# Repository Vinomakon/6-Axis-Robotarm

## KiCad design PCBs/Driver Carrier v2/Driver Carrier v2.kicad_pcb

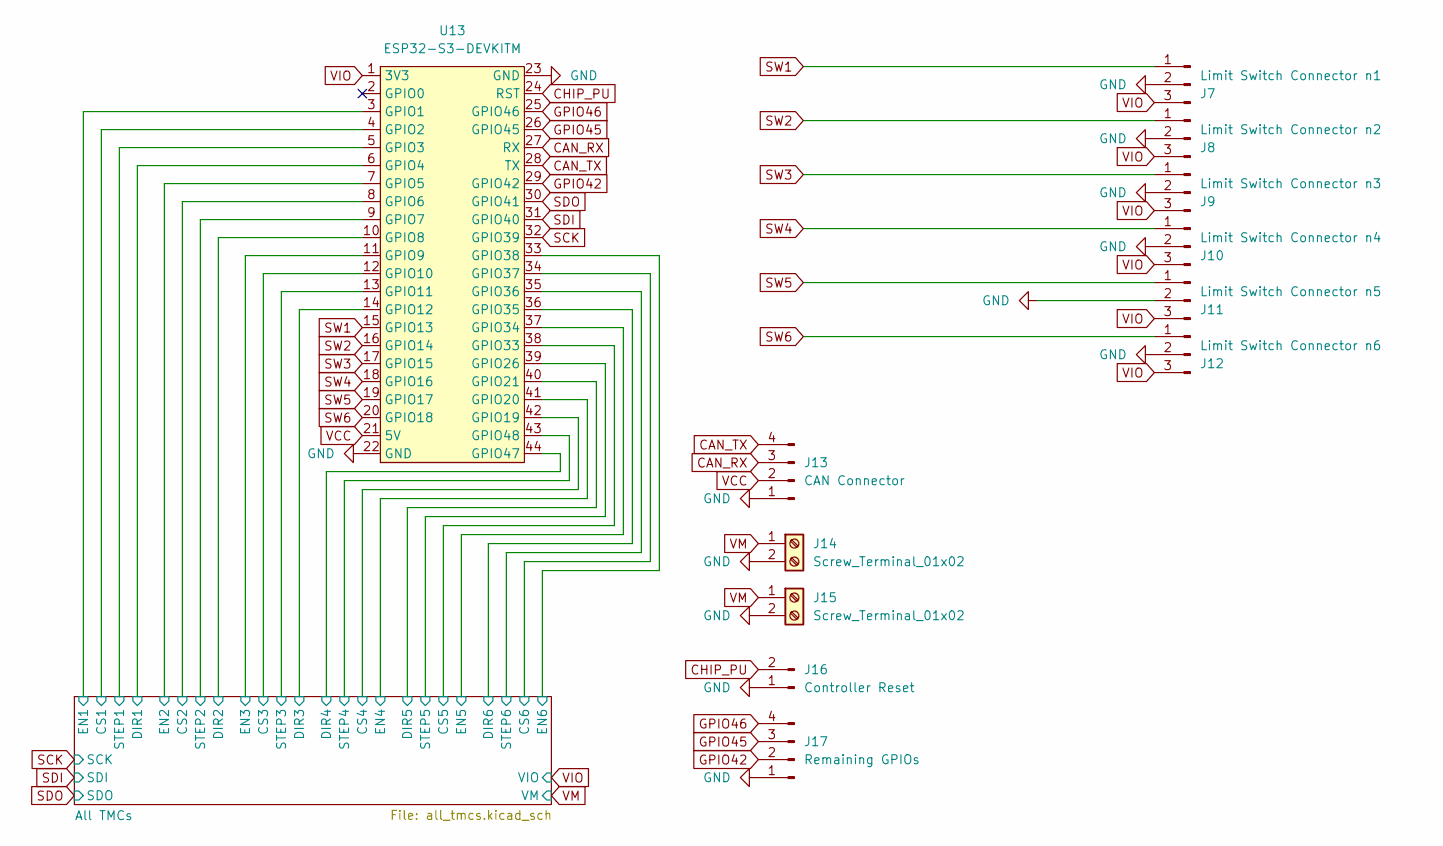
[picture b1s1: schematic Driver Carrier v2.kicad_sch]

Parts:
J7: Limit Switch Connector n1; PinHeader_1x03_P2.54mm_Vertical
J8: Limit Switch Connector n2; PinHeader_1x03_P2.54mm_Vertical
J9: Limit Switch Connector n3; PinHeader_1x03_P2.54mm_Vertical
J10: Limit Switch Connector n4; PinHeader_1x03_P2.54mm_Vertical
J11: Limit Switch Connector n5; PinHeader_1x03_P2.54mm_Vertical
J12: Limit Switch Connector n6; PinHeader_1x03_P2.54mm_Vertical
J13: CAN Connector; PinHeader_1x04_P2.54mm_Vertical
J14, J15: Screw_Terminal_01x02; Phoenix_TerminalBlock_1x02_3.5mm_1984617
J16: Controller Reset; PinHeader_1x02_P2.54mm_Vertical
J17: Remaining GPIOs; PinHeader_1x04_P2.54mm_Vertical
U13: ESP32-S3-DEVKITM; ESP32-S3-DEVKITM Female Headers

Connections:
/All TMCs/CS1: U13.4 (GPIO2); also elsewhere on the board
/All TMCs/CS2: U13.8 (GPIO6); also elsewhere on the board
/All TMCs/CS3: U13.12 (GPIO10); also elsewhere on the board
/All TMCs/CS4: U13.42 (GPIO19); also elsewhere on the board
/All TMCs/CS5: U13.38 (GPIO33); also elsewhere on the board
/All TMCs/CS6: U13.34 (GPIO37); also elsewhere on the board
/All TMCs/DIR1: U13.6 (GPIO4); also elsewhere on the board
/All TMCs/DIR2: U13.10 (GPIO8); also elsewhere on the board
/All TMCs/DIR3: U13.14 (GPIO12); also elsewhere on the board
/All TMCs/DIR4: U13.44 (GPIO47); also elsewhere on the board
/All TMCs/DIR5: U13.40 (GPIO21); also elsewhere on the board
/All TMCs/DIR6: U13.36 (GPIO35); also elsewhere on the board
/All TMCs/EN1: U13.3 (GPIO1); also elsewhere on the board
/All TMCs/EN2: U13.7 (GPIO5); also elsewhere on the board
/All TMCs/EN3: U13.11 (GPIO9); also elsewhere on the board
/All TMCs/EN4: U13.41 (GPIO20); also elsewhere on the board
/All TMCs/EN5: U13.37 (GPIO34); also elsewhere on the board
/All TMCs/EN6: U13.33 (GPIO38); also elsewhere on the board
/All TMCs/STEP1: U13.5 (GPIO3); also elsewhere on the board
/All TMCs/STEP2: U13.9 (GPIO7); also elsewhere on the board
/All TMCs/STEP3: U13.13 (GPIO11); also elsewhere on the board
/All TMCs/STEP4: U13.43 (GPIO48); also elsewhere on the board
/All TMCs/STEP5: U13.39 (GPIO26); also elsewhere on the board
/All TMCs/STEP6: U13.35 (GPIO36); also elsewhere on the board
CAN_RX: J13.3, U13.27 (RX)
CAN_TX: J13.4, U13.28 (TX)
CHIP_PU: J16.2, U13.24 (RST)
GND: J7.2, J8.2, J9.2, J10.2, J11.2, J12.2, J13.1, J14.2, J15.2, J16.1, J17.1, U13.22 (GND), U13.23 (GND); also elsewhere on the board
GPIO42: J17.2, U13.29 (GPIO42)
GPIO45: J17.3, U13.26 (GPIO45)
GPIO46: J17.4, U13.25 (GPIO46)
SCK: U13.32 (GPIO39); also elsewhere on the board
SDI: U13.31 (GPIO40); also elsewhere on the board
SDO: U13.30 (GPIO41); also elsewhere on the board
SW1: J7.1, U13.15 (GPIO13)
SW2: J8.1, U13.16 (GPIO14)
SW3: J9.1, U13.17 (GPIO15)
SW4: J10.1, U13.18 (GPIO16)
SW5: J11.1, U13.19 (GPIO17)
SW6: J12.1, U13.20 (GPIO18)
VCC: J13.2, U13.21 (5V)
VIO: J7.3, J8.3, J9.3, J10.3, J11.3, J12.3, U13.1 (3V3); also elsewhere on the board
VM: J14.1, J15.1; also elsewhere on the board

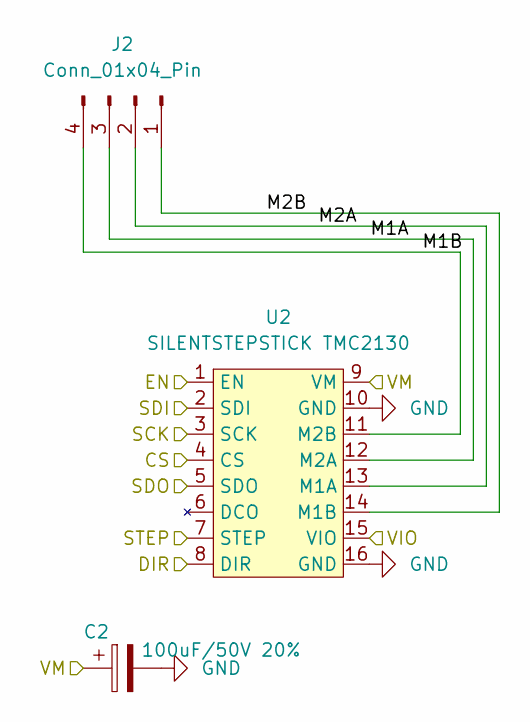
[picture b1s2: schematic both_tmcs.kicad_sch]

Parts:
C2: 100uF/50V 20%; CP_Radial_D8.0mm_P3.50mm
J2: Conn_01x04_Pin; PinHeader_1x04_P2.54mm_Vertical
U2: SILENTSTEPSTICK TMC2130; Digikey PartN TMCSILENTSTEPSTICK SPI

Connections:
/All TMCs/BothTMCs n2/M1A: J2.3, U2.12 (M2A)
/All TMCs/BothTMCs n2/M1B: J2.4, U2.11 (M2B)
/All TMCs/BothTMCs n2/M2A: J2.2, U2.13 (M1A)
/All TMCs/BothTMCs n2/M2B: J2.1, U2.14 (M1B)
/All TMCs/CS2: U2.4 (CS); also elsewhere on the board
/All TMCs/DIR2: U2.8 (DIR); also elsewhere on the board
/All TMCs/EN2: U2.1 (EN); also elsewhere on the board
/All TMCs/STEP2: U2.7 (STEP); also elsewhere on the board
GND: C2.2, U2.10 (GND), U2.16 (GND); also elsewhere on the board
SCK: U2.3 (SCK); also elsewhere on the board
SDI: U2.2 (SDI); also elsewhere on the board
SDO: U2.5 (SDO); also elsewhere on the board
VIO: U2.15 (VIO); also elsewhere on the board
VM: C2.1, U2.9 (VM); also elsewhere on the board

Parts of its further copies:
C1, C3, C4, C5, C6: 100uF/50V 20%; CP_Radial_D8.0mm_P3.50mm
J1, J3, J4, J5, J6: Conn_01x04_Pin; PinHeader_1x04_P2.54mm_Vertical
U1, U3, U4, U5, U6: SILENTSTEPSTICK TMC2130; Digikey PartN TMCSILENTSTEPSTICK SPI

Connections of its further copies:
/All TMCs/BothTMCs n1/M1A: J1.3, U1.12 (M2A)
/All TMCs/BothTMCs n1/M1B: J1.4, U1.11 (M2B)
/All TMCs/BothTMCs n1/M2A: J1.2, U1.13 (M1A)
/All TMCs/BothTMCs n1/M2B: J1.1, U1.14 (M1B)
/All TMCs/BothTMCs n3/M1A: J3.3, U3.12 (M2A)
/All TMCs/BothTMCs n3/M1B: J3.4, U3.11 (M2B)
/All TMCs/BothTMCs n3/M2A: J3.2, U3.13 (M1A)
/All TMCs/BothTMCs n3/M2B: J3.1, U3.14 (M1B)
/All TMCs/BothTMCs n4/M1A: J4.3, U4.12 (M2A)
/All TMCs/BothTMCs n4/M1B: J4.4, U4.11 (M2B)
/All TMCs/BothTMCs n4/M2A: J4.2, U4.13 (M1A)
/All TMCs/BothTMCs n4/M2B: J4.1, U4.14 (M1B)
/All TMCs/BothTMCs n5/M1A: J5.3, U5.12 (M2A)
/All TMCs/BothTMCs n5/M1B: J5.4, U5.11 (M2B)
/All TMCs/BothTMCs n5/M2A: J5.2, U5.13 (M1A)
/All TMCs/BothTMCs n5/M2B: J5.1, U5.14 (M1B)
/All TMCs/BothTMCs n6/M1A: J6.3, U6.12 (M2A)
/All TMCs/BothTMCs n6/M1B: J6.4, U6.11 (M2B)
/All TMCs/BothTMCs n6/M2A: J6.2, U6.13 (M1A)
/All TMCs/BothTMCs n6/M2B: J6.1, U6.14 (M1B)
/All TMCs/CS1: U1.4 (CS); also elsewhere on the board
/All TMCs/CS3: U3.4 (CS); also elsewhere on the board
/All TMCs/CS4: U4.4 (CS); also elsewhere on the board
/All TMCs/CS5: U5.4 (CS); also elsewhere on the board
/All TMCs/CS6: U6.4 (CS); also elsewhere on the board
/All TMCs/DIR1: U1.8 (DIR); also elsewhere on the board
/All TMCs/DIR3: U3.8 (DIR); also elsewhere on the board
/All TMCs/DIR4: U4.8 (DIR); also elsewhere on the board
/All TMCs/DIR5: U5.8 (DIR); also elsewhere on the board
/All TMCs/DIR6: U6.8 (DIR); also elsewhere on the board
/All TMCs/EN1: U1.1 (EN); also elsewhere on the board
/All TMCs/EN3: U3.1 (EN); also elsewhere on the board
/All TMCs/EN4: U4.1 (EN); also elsewhere on the board
/All TMCs/EN5: U5.1 (EN); also elsewhere on the board
/All TMCs/EN6: U6.1 (EN); also elsewhere on the board
/All TMCs/STEP1: U1.7 (STEP); also elsewhere on the board
/All TMCs/STEP3: U3.7 (STEP); also elsewhere on the board
/All TMCs/STEP4: U4.7 (STEP); also elsewhere on the board
/All TMCs/STEP5: U5.7 (STEP); also elsewhere on the board
/All TMCs/STEP6: U6.7 (STEP); also elsewhere on the board
GND: C1.2, C3.2, C4.2, C5.2, C6.2, U1.10 (GND), U1.16 (GND), U3.10 (GND), U3.16 (GND), U4.10 (GND), U4.16 (GND), U5.10 (GND), U5.16 (GND), U6.10 (GND), U6.16 (GND); also elsewhere on the board
SCK: U1.3 (SCK), U3.3 (SCK), U4.3 (SCK), U5.3 (SCK), U6.3 (SCK); also elsewhere on the board
SDI: U1.2 (SDI), U3.2 (SDI), U4.2 (SDI), U5.2 (SDI), U6.2 (SDI); also elsewhere on the board
SDO: U1.5 (SDO), U3.5 (SDO), U4.5 (SDO), U5.5 (SDO), U6.5 (SDO); also elsewhere on the board
VIO: U1.15 (VIO), U3.15 (VIO), U4.15 (VIO), U5.15 (VIO), U6.15 (VIO); also elsewhere on the board
VM: C1.1, C3.1, C4.1, C5.1, C6.1, U1.9 (VM), U3.9 (VM), U4.9 (VM), U5.9 (VM), U6.9 (VM); also elsewhere on the board

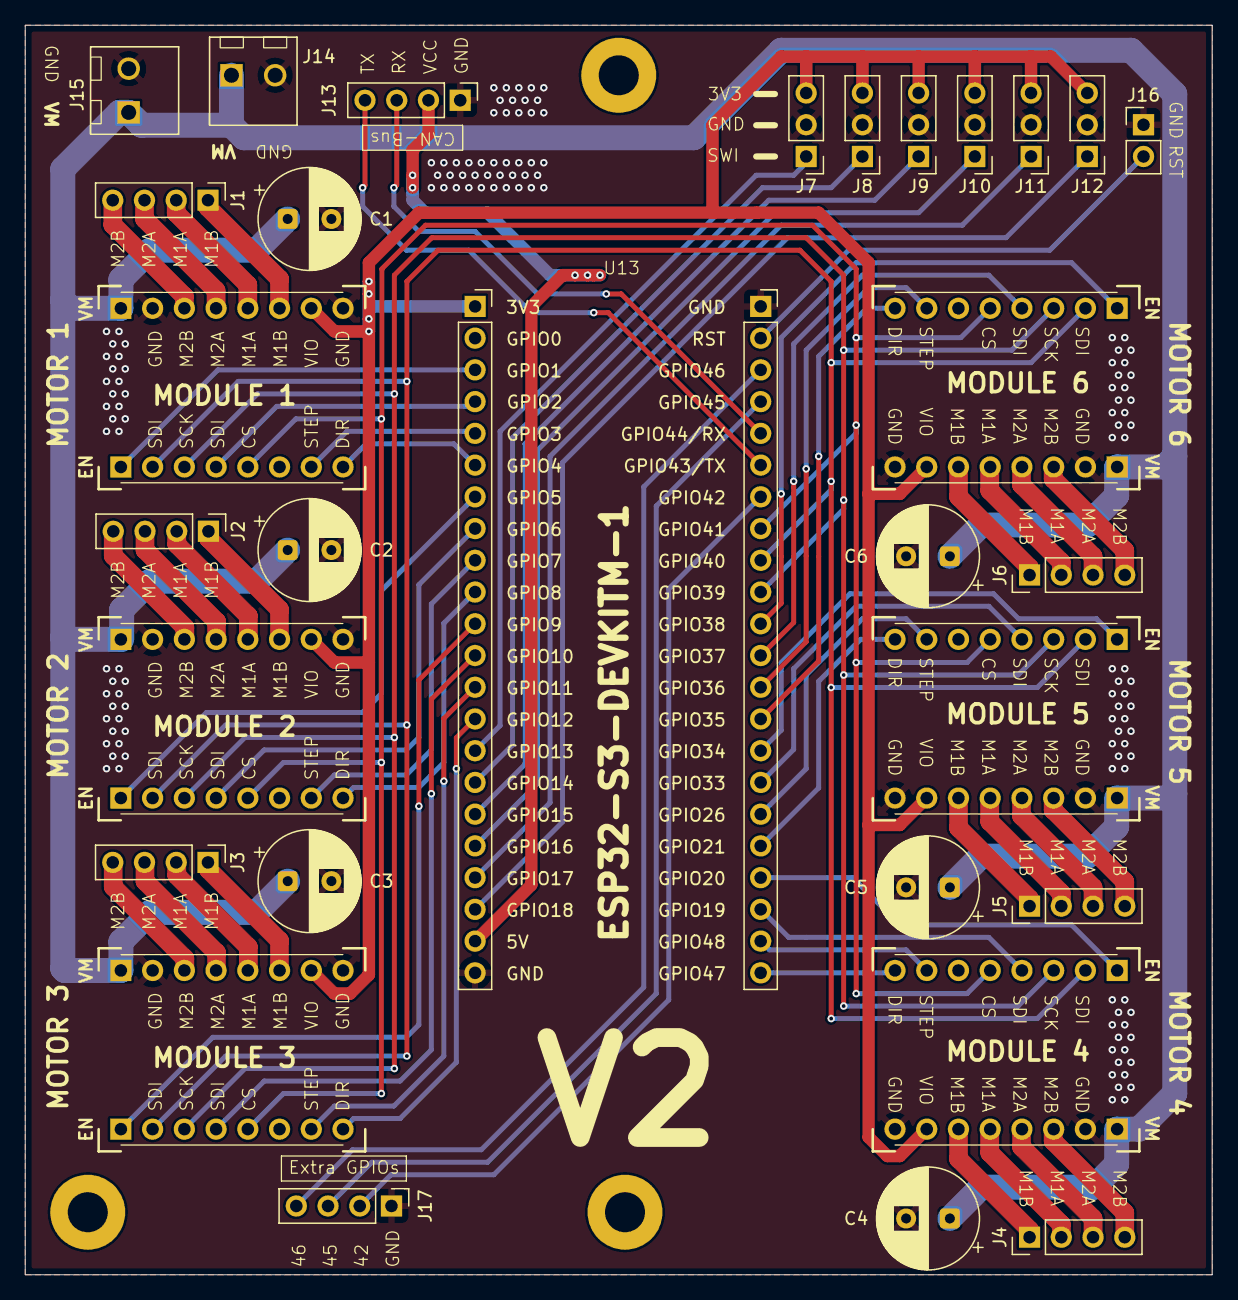
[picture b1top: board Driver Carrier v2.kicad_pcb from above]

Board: 2 copper layers, 95.0 x 100.0 mm, 30 parts (0 on the bottom side), 67 nets.

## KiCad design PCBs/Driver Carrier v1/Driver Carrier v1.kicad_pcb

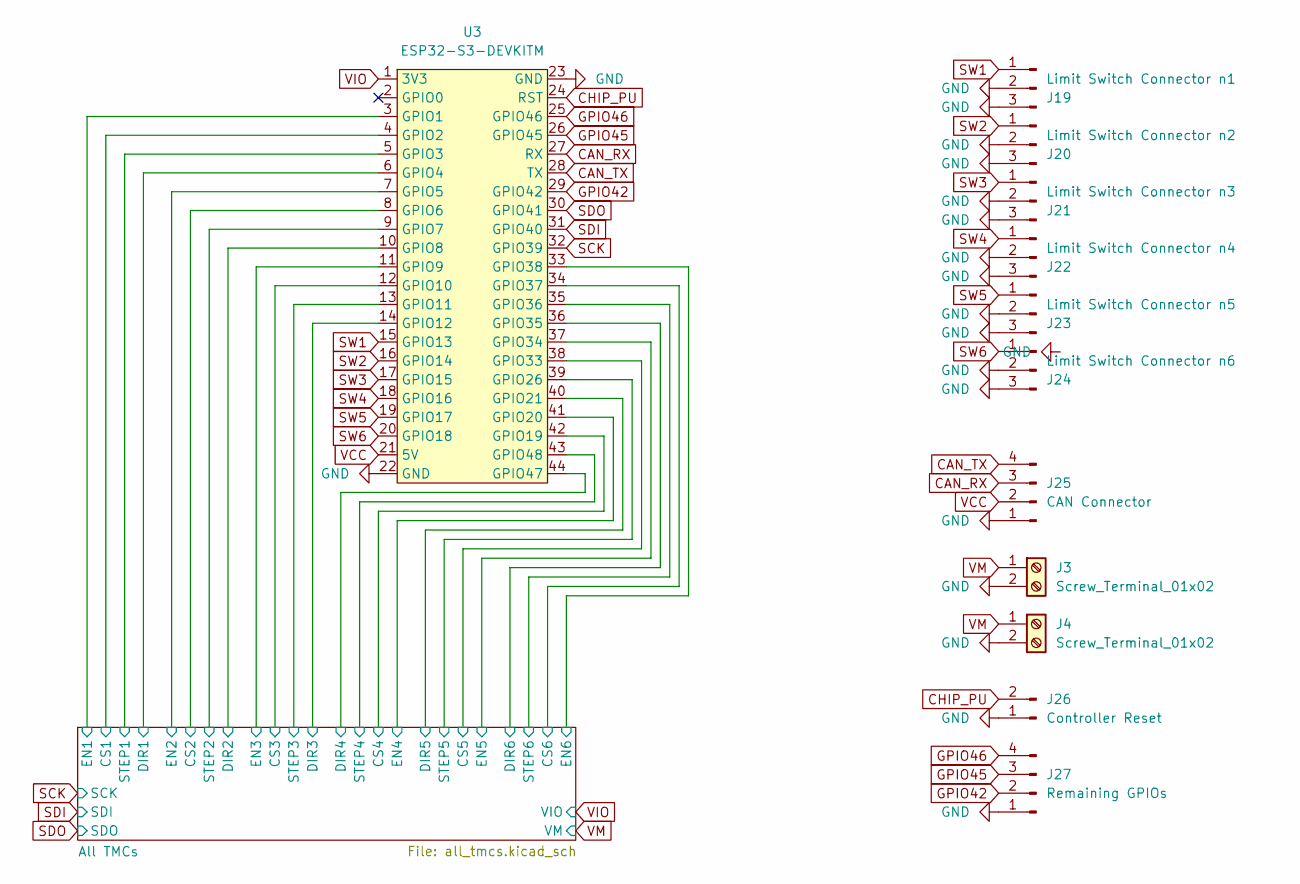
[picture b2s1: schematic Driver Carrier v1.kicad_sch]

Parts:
J3, J4: Screw_Terminal_01x02; Phoenix_TerminalBlock_1x02_3.5mm_1984617
J19: Limit Switch Connector n1; PinHeader_1x03_P2.54mm_Vertical
J20: Limit Switch Connector n2; PinHeader_1x03_P2.54mm_Vertical
J21: Limit Switch Connector n3; PinHeader_1x03_P2.54mm_Vertical
J22: Limit Switch Connector n4; PinHeader_1x03_P2.54mm_Vertical
J23: Limit Switch Connector n5; PinHeader_1x03_P2.54mm_Vertical
J24: Limit Switch Connector n6; PinHeader_1x03_P2.54mm_Vertical
J25: CAN Connector; PinHeader_1x04_P2.54mm_Vertical
J26: Controller Reset; PinHeader_1x02_P2.54mm_Vertical
J27: Remaining GPIOs; PinHeader_1x04_P2.54mm_Vertical
U3: ESP32-S3-DEVKITM; ESP32-S3-DEVKITM Female Headers

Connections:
/All TMCs/CS1: U3.4 (GPIO2); also elsewhere on the board
/All TMCs/CS2: U3.8 (GPIO6); also elsewhere on the board
/All TMCs/CS3: U3.12 (GPIO10); also elsewhere on the board
/All TMCs/CS4: U3.42 (GPIO19); also elsewhere on the board
/All TMCs/CS5: U3.38 (GPIO33); also elsewhere on the board
/All TMCs/CS6: U3.34 (GPIO37); also elsewhere on the board
/All TMCs/DIR1: U3.6 (GPIO4); also elsewhere on the board
/All TMCs/DIR2: U3.10 (GPIO8); also elsewhere on the board
/All TMCs/DIR3: U3.14 (GPIO12); also elsewhere on the board
/All TMCs/DIR4: U3.44 (GPIO47); also elsewhere on the board
/All TMCs/DIR5: U3.40 (GPIO21); also elsewhere on the board
/All TMCs/DIR6: U3.36 (GPIO35); also elsewhere on the board
/All TMCs/EN1: U3.3 (GPIO1); also elsewhere on the board
/All TMCs/EN2: U3.7 (GPIO5); also elsewhere on the board
/All TMCs/EN3: U3.11 (GPIO9); also elsewhere on the board
/All TMCs/EN4: U3.41 (GPIO20); also elsewhere on the board
/All TMCs/EN5: U3.37 (GPIO34); also elsewhere on the board
/All TMCs/EN6: U3.33 (GPIO38); also elsewhere on the board
/All TMCs/STEP1: U3.5 (GPIO3); also elsewhere on the board
/All TMCs/STEP2: U3.9 (GPIO7); also elsewhere on the board
/All TMCs/STEP3: U3.13 (GPIO11); also elsewhere on the board
/All TMCs/STEP4: U3.43 (GPIO48); also elsewhere on the board
/All TMCs/STEP5: U3.39 (GPIO26); also elsewhere on the board
/All TMCs/STEP6: U3.35 (GPIO36); also elsewhere on the board
CAN_RX: J25.3, U3.27 (RX)
CAN_TX: J25.4, U3.28 (TX)
CHIP_PU: J26.2, U3.24 (RST)
GND: J3.2, J4.2, J19.2, J19.3, J20.2, J20.3, J21.2, J21.3, J22.2, J22.3, J23.2, J23.3, J24.2, J24.3, J25.1, J26.1, J27.1, U3.22 (GND), U3.23 (GND); also elsewhere on the board
GPIO42: J27.2, U3.29 (GPIO42)
GPIO45: J27.3, U3.26 (GPIO45)
GPIO46: J27.4, U3.25 (GPIO46)
SCK: U3.32 (GPIO39); also elsewhere on the board
SDI: U3.31 (GPIO40); also elsewhere on the board
SDO: U3.30 (GPIO41); also elsewhere on the board
SW1: J19.1, U3.15 (GPIO13)
SW2: J20.1, U3.16 (GPIO14)
SW3: J21.1, U3.17 (GPIO15)
SW4: J22.1, U3.18 (GPIO16)
SW5: J23.1, U3.19 (GPIO17)
SW6: J24.1, U3.20 (GPIO18)
VCC: J25.2, U3.21 (5V)
VIO: U3.1 (3V3); also elsewhere on the board
VM: J3.1, J4.1; also elsewhere on the board

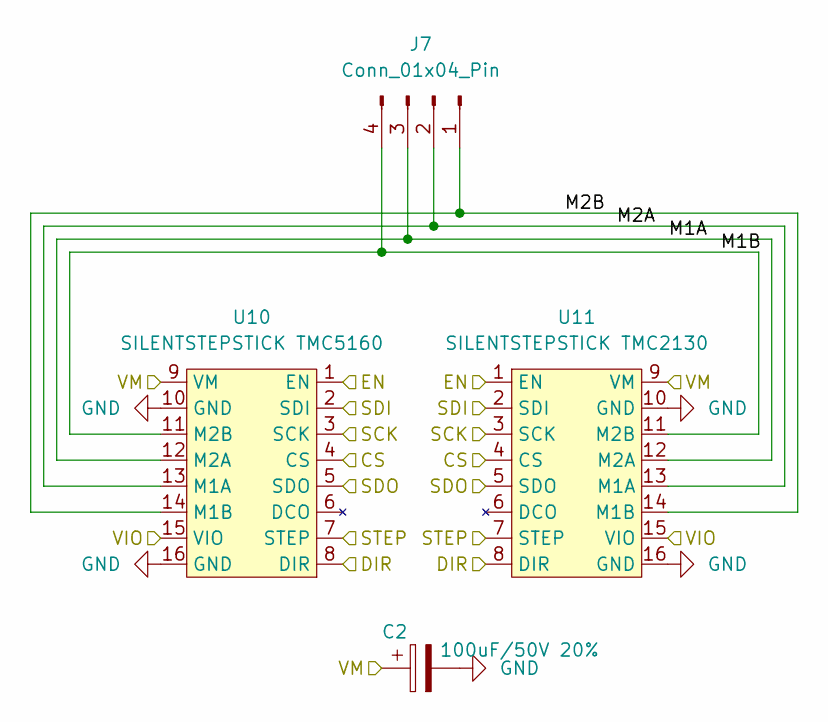
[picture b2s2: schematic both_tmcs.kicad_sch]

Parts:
C2: 100uF/50V 20%; CP_Radial_D8.0mm_P3.50mm
J7: Conn_01x04_Pin; PinHeader_1x04_P2.54mm_Vertical
U10: SILENTSTEPSTICK TMC5160; Digikey PartN TMC5160SILENTSTEPSTICK
U11: SILENTSTEPSTICK TMC2130; Digikey PartN TMCSILENTSTEPSTICK SPI

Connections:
/All TMCs/BothTMCs n2/M1A: J7.3, U10.12 (M2A), U11.12 (M2A)
/All TMCs/BothTMCs n2/M1B: J7.4, U10.11 (M2B), U11.11 (M2B)
/All TMCs/BothTMCs n2/M2A: J7.2, U10.13 (M1A), U11.13 (M1A)
/All TMCs/BothTMCs n2/M2B: J7.1, U10.14 (M1B), U11.14 (M1B)
/All TMCs/CS2: U10.4 (CS), U11.4 (CS); also elsewhere on the board
/All TMCs/DIR2: U10.8 (DIR), U11.8 (DIR); also elsewhere on the board
/All TMCs/EN2: U10.1 (EN), U11.1 (EN); also elsewhere on the board
/All TMCs/STEP2: U10.7 (STEP), U11.7 (STEP); also elsewhere on the board
GND: C2.2, U10.10 (GND), U10.16 (GND), U11.10 (GND), U11.16 (GND); also elsewhere on the board
SCK: U10.3 (SCK), U11.3 (SCK); also elsewhere on the board
SDI: U10.2 (SDI), U11.2 (SDI); also elsewhere on the board
SDO: U10.5 (SDO), U11.5 (SDO); also elsewhere on the board
VIO: U10.15 (VIO), U11.15 (VIO); also elsewhere on the board
VM: C2.1, U10.9 (VM), U11.9 (VM); also elsewhere on the board

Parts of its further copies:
C1, C3, C4, C5, C6: 100uF/50V 20%; CP_Radial_D8.0mm_P3.50mm
J6, J8, J9, J10, J11: Conn_01x04_Pin; PinHeader_1x04_P2.54mm_Vertical
U8, U12, U14, U16, U18: SILENTSTEPSTICK TMC5160; Digikey PartN TMC5160SILENTSTEPSTICK
U9, U13, U15, U17, U19: SILENTSTEPSTICK TMC2130; Digikey PartN TMCSILENTSTEPSTICK SPI

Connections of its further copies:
/All TMCs/BothTMCs n1/M1A: J6.3, U8.12 (M2A), U9.12 (M2A)
/All TMCs/BothTMCs n1/M1B: J6.4, U8.11 (M2B), U9.11 (M2B)
/All TMCs/BothTMCs n1/M2A: J6.2, U8.13 (M1A), U9.13 (M1A)
/All TMCs/BothTMCs n1/M2B: J6.1, U8.14 (M1B), U9.14 (M1B)
/All TMCs/BothTMCs n3/M1A: J10.3, U16.12 (M2A), U17.12 (M2A)
/All TMCs/BothTMCs n3/M1B: J10.4, U16.11 (M2B), U17.11 (M2B)
/All TMCs/BothTMCs n3/M2A: J10.2, U16.13 (M1A), U17.13 (M1A)
/All TMCs/BothTMCs n3/M2B: J10.1, U16.14 (M1B), U17.14 (M1B)
/All TMCs/BothTMCs n4/M1A: J8.3, U12.12 (M2A), U13.12 (M2A)
/All TMCs/BothTMCs n4/M1B: J8.4, U12.11 (M2B), U13.11 (M2B)
/All TMCs/BothTMCs n4/M2A: J8.2, U12.13 (M1A), U13.13 (M1A)
/All TMCs/BothTMCs n4/M2B: J8.1, U12.14 (M1B), U13.14 (M1B)
/All TMCs/BothTMCs n5/M1A: J9.3, U14.12 (M2A), U15.12 (M2A)
/All TMCs/BothTMCs n5/M1B: J9.4, U14.11 (M2B), U15.11 (M2B)
/All TMCs/BothTMCs n5/M2A: J9.2, U14.13 (M1A), U15.13 (M1A)
/All TMCs/BothTMCs n5/M2B: J9.1, U14.14 (M1B), U15.14 (M1B)
/All TMCs/BothTMCs n6/M1A: J11.3, U18.12 (M2A), U19.12 (M2A)
/All TMCs/BothTMCs n6/M1B: J11.4, U18.11 (M2B), U19.11 (M2B)
/All TMCs/BothTMCs n6/M2A: J11.2, U18.13 (M1A), U19.13 (M1A)
/All TMCs/BothTMCs n6/M2B: J11.1, U18.14 (M1B), U19.14 (M1B)
/All TMCs/CS1: U8.4 (CS), U9.4 (CS); also elsewhere on the board
/All TMCs/CS3: U16.4 (CS), U17.4 (CS); also elsewhere on the board
/All TMCs/CS4: U12.4 (CS), U13.4 (CS); also elsewhere on the board
/All TMCs/CS5: U14.4 (CS), U15.4 (CS); also elsewhere on the board
/All TMCs/CS6: U18.4 (CS), U19.4 (CS); also elsewhere on the board
/All TMCs/DIR1: U8.8 (DIR), U9.8 (DIR); also elsewhere on the board
/All TMCs/DIR3: U16.8 (DIR), U17.8 (DIR); also elsewhere on the board
/All TMCs/DIR4: U12.8 (DIR), U13.8 (DIR); also elsewhere on the board
/All TMCs/DIR5: U14.8 (DIR), U15.8 (DIR); also elsewhere on the board
/All TMCs/DIR6: U18.8 (DIR), U19.8 (DIR); also elsewhere on the board
/All TMCs/EN1: U8.1 (EN), U9.1 (EN); also elsewhere on the board
/All TMCs/EN3: U16.1 (EN), U17.1 (EN); also elsewhere on the board
/All TMCs/EN4: U12.1 (EN), U13.1 (EN); also elsewhere on the board
/All TMCs/EN5: U14.1 (EN), U15.1 (EN); also elsewhere on the board
/All TMCs/EN6: U18.1 (EN), U19.1 (EN); also elsewhere on the board
/All TMCs/STEP1: U8.7 (STEP), U9.7 (STEP); also elsewhere on the board
/All TMCs/STEP3: U16.7 (STEP), U17.7 (STEP); also elsewhere on the board
/All TMCs/STEP4: U12.7 (STEP), U13.7 (STEP); also elsewhere on the board
/All TMCs/STEP5: U14.7 (STEP), U15.7 (STEP); also elsewhere on the board
/All TMCs/STEP6: U18.7 (STEP), U19.7 (STEP); also elsewhere on the board
GND: C1.2, C3.2, C4.2, C5.2, C6.2, U8.10 (GND), U8.16 (GND), U9.10 (GND), U9.16 (GND), U12.10 (GND), U12.16 (GND), U13.10 (GND), U13.16 (GND), U14.10 (GND), U14.16 (GND), U15.10 (GND), U15.16 (GND), U16.10 (GND), U16.16 (GND), U17.10 (GND), U17.16 (GND), U18.10 (GND), U18.16 (GND), U19.10 (GND), U19.16 (GND); also elsewhere on the board
SCK: U8.3 (SCK), U9.3 (SCK), U12.3 (SCK), U13.3 (SCK), U14.3 (SCK), U15.3 (SCK), U16.3 (SCK), U17.3 (SCK), U18.3 (SCK), U19.3 (SCK); also elsewhere on the board
SDI: U8.2 (SDI), U9.2 (SDI), U12.2 (SDI), U13.2 (SDI), U14.2 (SDI), U15.2 (SDI), U16.2 (SDI), U17.2 (SDI), U18.2 (SDI), U19.2 (SDI); also elsewhere on the board
SDO: U8.5 (SDO), U9.5 (SDO), U12.5 (SDO), U13.5 (SDO), U14.5 (SDO), U15.5 (SDO), U16.5 (SDO), U17.5 (SDO), U18.5 (SDO), U19.5 (SDO); also elsewhere on the board
VIO: U8.15 (VIO), U9.15 (VIO), U12.15 (VIO), U13.15 (VIO), U14.15 (VIO), U15.15 (VIO), U16.15 (VIO), U17.15 (VIO), U18.15 (VIO), U19.15 (VIO); also elsewhere on the board
VM: C1.1, C3.1, C4.1, C5.1, C6.1, U8.9 (VM), U9.9 (VM), U12.9 (VM), U13.9 (VM), U14.9 (VM), U15.9 (VM), U16.9 (VM), U17.9 (VM), U18.9 (VM), U19.9 (VM); also elsewhere on the board

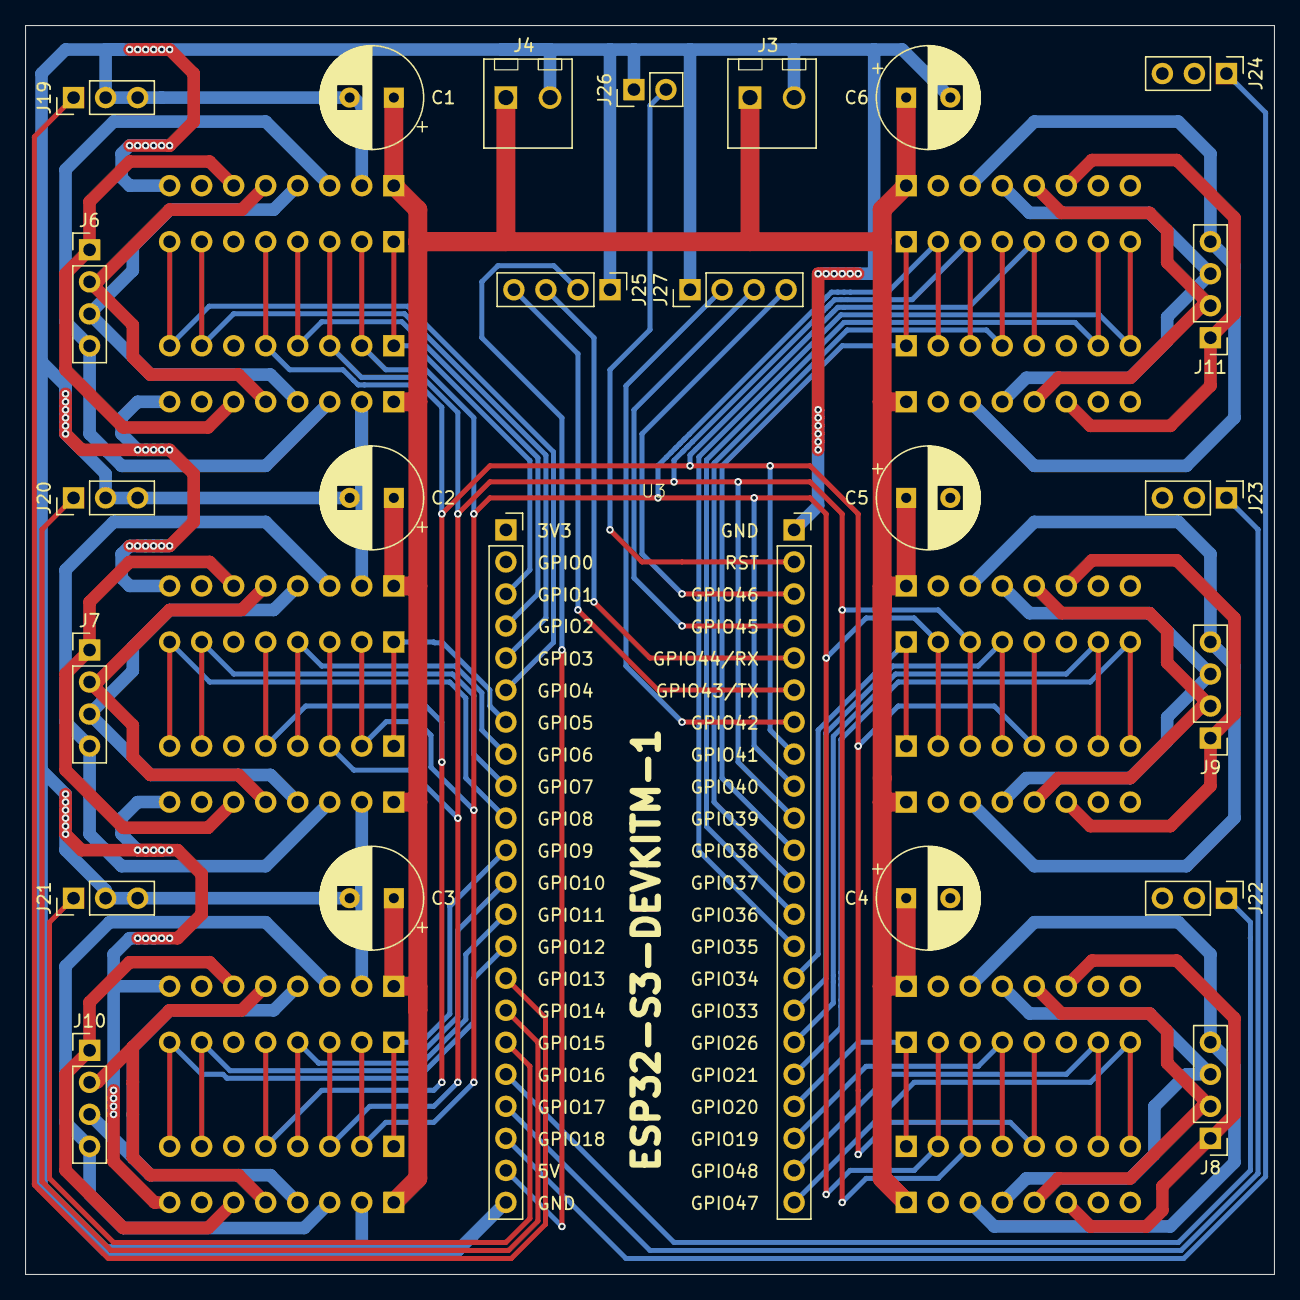
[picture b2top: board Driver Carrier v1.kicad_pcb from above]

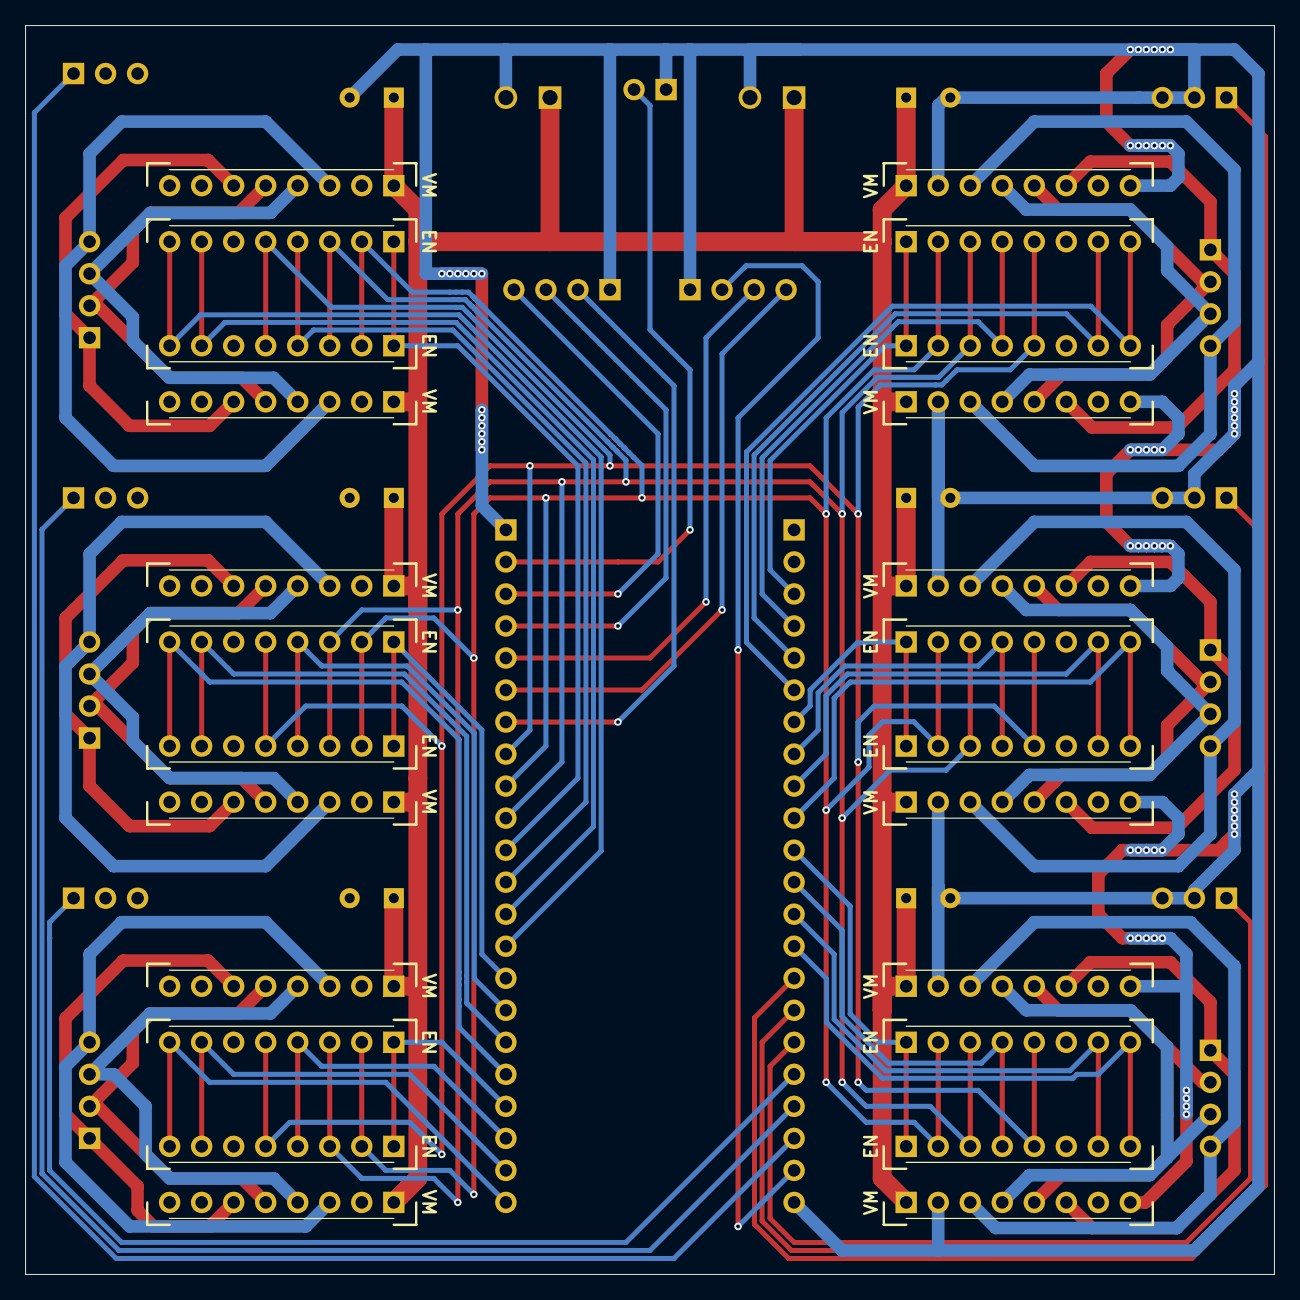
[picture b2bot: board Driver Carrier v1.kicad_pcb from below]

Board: 2 copper layers, 99.1 x 99.1 mm, 36 parts (12 on the bottom side), 67 nets.

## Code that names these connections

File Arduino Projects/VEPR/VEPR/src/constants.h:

// PINS FOR TMC-SPI
#define SDO_PIN 41
#define SCK_PIN 39
#define SDI_PIN 40

// PINS FOR MOTOR 1
#define DIR0_PIN 4
#define STEP0_PIN 3
#define EN0_PIN 1
#define CS0_PIN 2
#define SW0_PIN 13

// PINS FOR MOTOR 2
#define DIR1_PIN 8
#define STEP1_PIN 7
#define EN1_PIN 5
#define CS1_PIN 6
#define SW1_PIN 14

//PINS FOR MOTOR 3
#define DIR2_PIN 12
#define STEP2_PIN 11
#define EN2_PIN 9
#define CS2_PIN 10
#define SW2_PIN 15

//PINS FOR MOTOR 4
#define DIR3_PIN 47
#define STEP3_PIN 48
#define EN3_PIN 20
#define CS3_PIN 19
#define SW3_PIN 16

//PINS FOR MOTOR 5
#define DIR4_PIN 21
#define STEP4_PIN 26
#define EN4_PIN 34
#define CS4_PIN 33
#define SW4_PIN 17

//PINS FOR MOTOR 6
#define DIR5_PIN 35
#define STEP5_PIN 36
#define EN5_PIN 38
#define CS5_PIN 37
#define SW5_PIN 18

// VALUES FOR TMC
#define STALL_VALUE 15
#define R_SENSE 0.11f

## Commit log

2025-02-11 Commit Date: 11/2/2025
    Some small changes to the websockets code
2025-02-12 Added Homing Functionality
2025-02-12 Organization of Files
2025-02-13 Rewrote Main Code
    Instead of using my own code, I used the libraries "AccelStepper", "TMCStepper" and the built-in SPI function.
2025-02-14 Small Adjustments
2025-02-20 Added Big Motors
2025-02-20 Some little Improvements
2025-02-21 Integration of 3 more motors
    Still need to implement the synchrounous movement
2025-02-24 Started work on the next Carrier Board
2025-02-25 Continued working on the PCB
2025-02-26 Finished Driver Carrier
2025-02-26 Update Arbeitsjournal
2025-02-27 Unknown Changes
2025-04-14 Commit 14.04.2025
2025-04-16 New PCB and testing belt drive
2025-07-15 Progress 15.07
    A LOOOT of new things
2025-07-22 6th Motor Addition
    Python and Arduino
2025-07-22 6th Arm finished
2025-07-23 UI Redesign v1
2025-07-24 Heavy changes to the python script and C++ code
2025-07-24 hotfix individualmovement
2025-07-25 A looooooooooooot of Paramteres
2025-07-25 Kindofworking
2025-07-25 Current Limiting fix
2025-07-25 Splitting the parameter submission
2025-07-31 Preparing for 3rd prototype
    Preparing for 3rd prototype and starting work on Arm0
2025-08-07 python hotfix
2025-08-08 changed config
2025-08-08 MILESTONE Working Prototype
2025-08-08 new config
2025-08-10 Started testing with implementation of IK
    Currently on figuring out, how to calculate the needed position
2025-08-11 ik testing 2
2025-08-11 ik testing 3
2025-08-11 IK testing 4
    Added a new python script with a custom class, specifically to handle vectors in 3d space
2025-08-12 Successfull theoretical IK
2025-08-12 iiii
2025-08-17 Better Cable Management
2025-08-18 Changed Pin-Out
2025-08-18 Added Arm0 Limit Switch Actuator
2025-08-21 Implemented IK into UI
    Have not tested it out yet, because of a broken variable power supply
2025-09-03 First Iteration of Report
2025-09-12 New LaTeX graphics
2025-09-14 More Latex graphics
2025-09-15 started a new implementation of IK in python
2025-09-16 Working Links
2025-09-16 Continued work on implementing IK
2025-09-16 Work in progress
2025-09-17 continuation v1
2025-09-17 changed ik
2025-09-21 Renewed some Solidworks Models
2025-10-08 A lot has changed :(
2025-10-09 ik heeeeelp
2025-10-09 Hopefully working ik
2025-10-09 The three fisrt links work, the last ones dont
2025-10-09 AAAAA i hate python
2025-10-09 I hate python even more than before
2025-10-10 IT IS ALIVE
2025-10-10 On the way
2025-10-11 New LaTeX Documentation
2025-10-27 aaaaaaaaaa
2025-12-26 Software version 2.0
2025-12-26 Finished UI Side for VEPR Software
2025-12-27 Updated UI
2025-12-27 Tested UI
    Acceleration and Speed Structure still seems a bit weird
2026-01-07 theoretical automations
